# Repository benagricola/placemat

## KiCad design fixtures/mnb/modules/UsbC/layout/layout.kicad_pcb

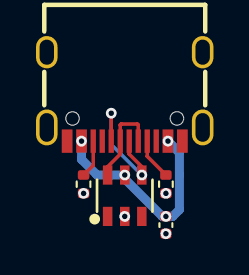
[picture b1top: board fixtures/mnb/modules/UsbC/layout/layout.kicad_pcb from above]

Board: 2 copper layers, 5 parts (0 on the bottom side), 6 nets.

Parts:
C1: C0402C105K9PACTU; C_0402_1005Metric
D1: USBLC6-2SC6; SOT-23-6_L2.9-W1.6-P0.95-LS2.8-BL
R1, R2: ERJ-2RKF5101X; R_0402_1005Metric
USBC1: TYPE-C-31-M-12; USB-C_SMD-TYPE-C-31-M-12_1

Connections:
USB_CC1: R1.1, USBC1.A5
USB_CC2: R2.1, USBC1.B5
USB_CONN_N: D1.6, USBC1.A7, USBC1.B7
USB_CONN_P: D1.4, USBC1.A6, USBC1.B6
VBUS: C1.1, D1.5, USBC1.A4B9, USBC1.B4A9
gnd: C1.2, D1.2, R1.2, R2.2, USBC1.1, USBC1.2, USBC1.3, USBC1.4, USBC1.A1B12, USBC1.B1A12

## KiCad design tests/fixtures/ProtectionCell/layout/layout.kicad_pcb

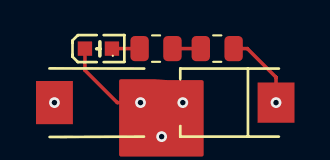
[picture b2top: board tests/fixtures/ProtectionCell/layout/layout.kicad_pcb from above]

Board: 2 copper layers, 5 parts (0 on the bottom side), 4 nets.

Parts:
D1: SS510B; SMB_L4.6-W3.5-LS5.3-RD
D2: SMBJ33CA; SMB_L4.6-W3.6-LS5.3-BI
D3: KT-0603Y; LED0603-R-RD_C2287
R1, R2: 1.3k; R_0805_2012Metric

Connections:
PROT_LED_MID: D3.1, R2.2
PROT_LED_RMID: R1.2, R2.1
v_out: D1.2, D2.1, D3.2
v_supply: D1.1, R1.1
